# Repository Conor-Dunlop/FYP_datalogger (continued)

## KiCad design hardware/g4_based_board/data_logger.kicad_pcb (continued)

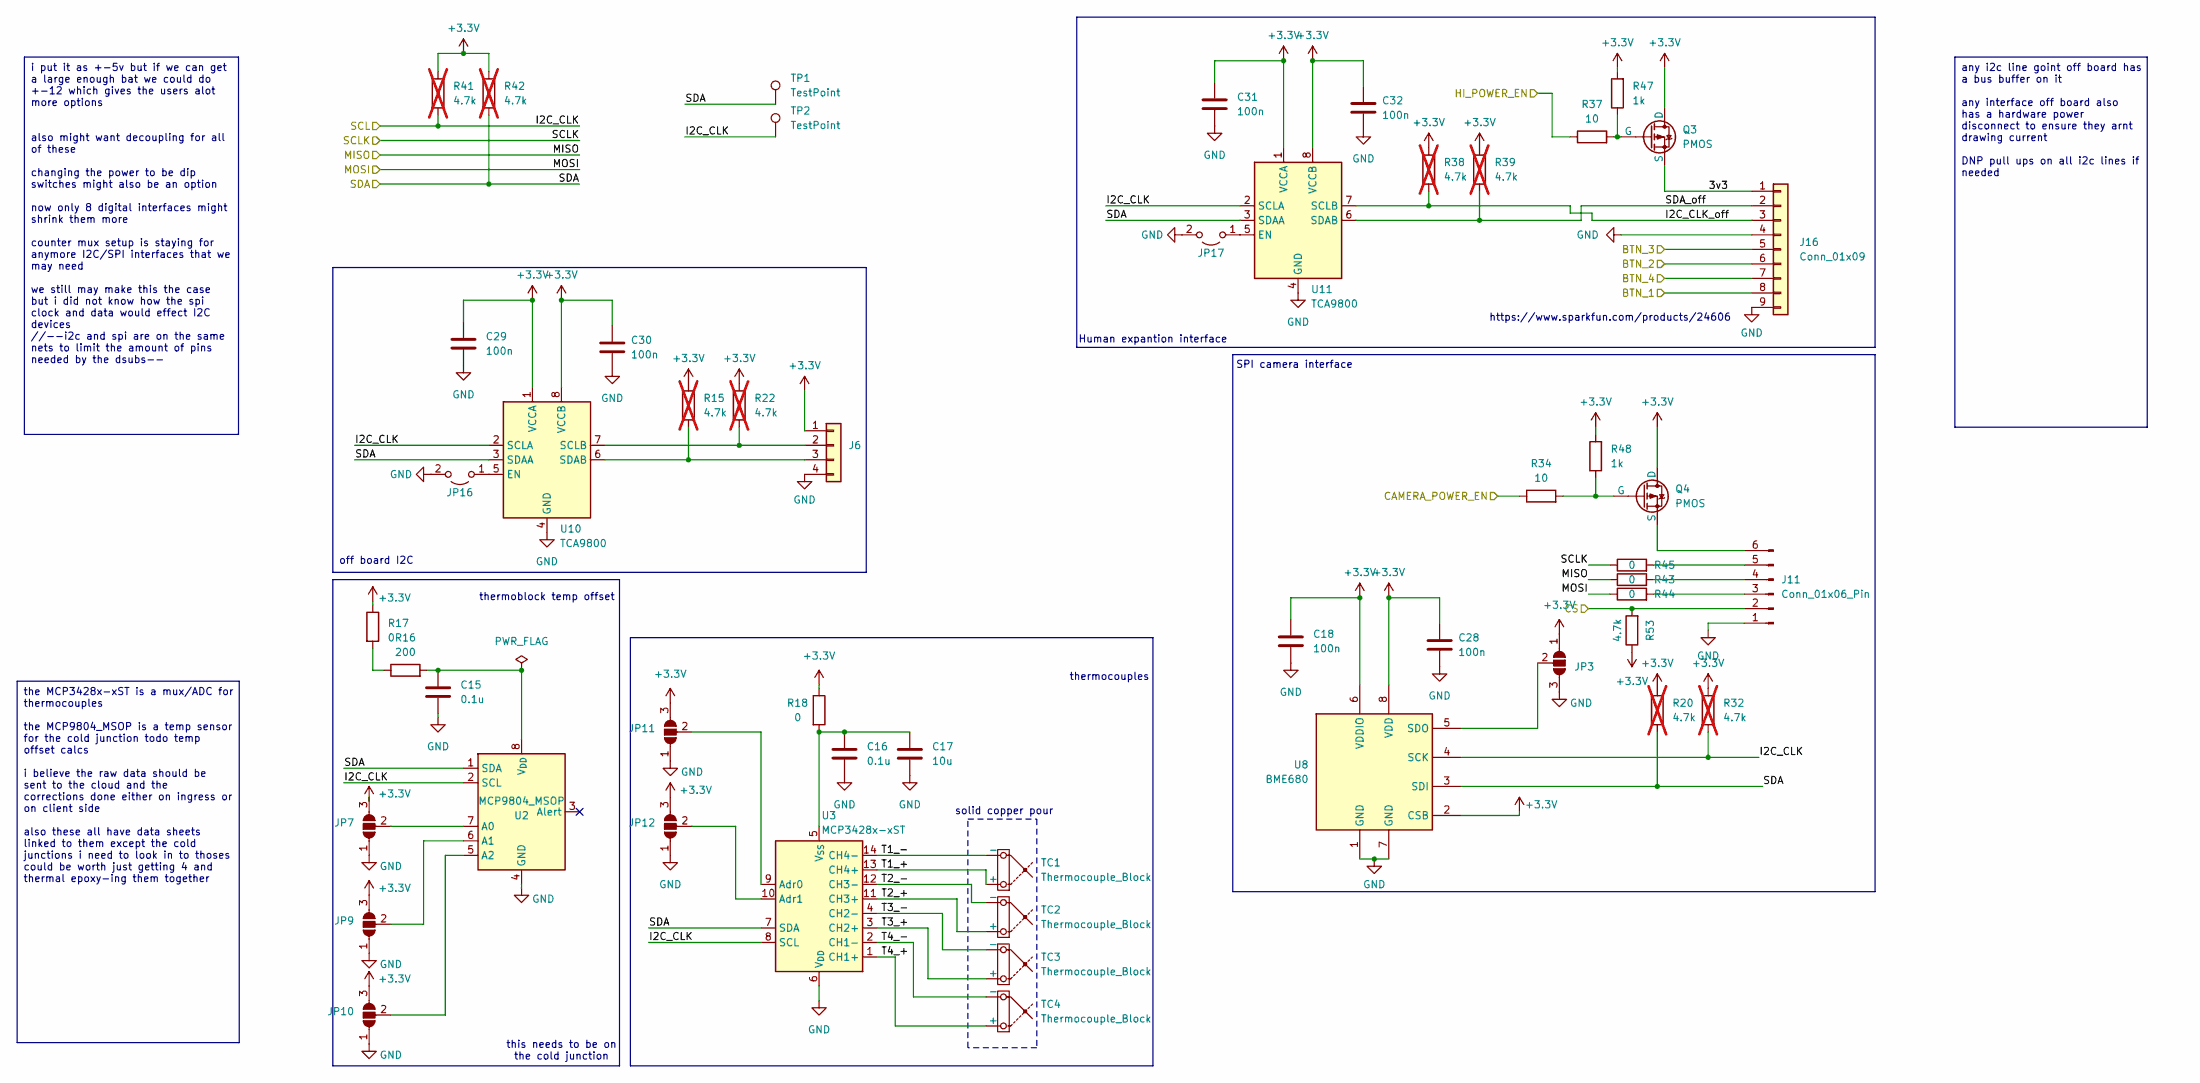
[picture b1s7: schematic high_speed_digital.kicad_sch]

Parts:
C15, C16: 0.1u; C_0603_1608Metric_Pad1.08x0.95mm_HandSolder
C17: 10u; C_0603_1608Metric_Pad1.08x0.95mm_HandSolder
C18, C28, C29, C30, C31, C32: 100n; C_0603_1608Metric_Pad1.08x0.95mm_HandSolder
J6: Conn_01x04; PinHeader_1x04_P2.54mm_Vertical
J11: Conn_01x06_Pin; JST_XH_B6B-XH-A_1x06_P2.50mm_Vertical
J16: Conn_01x09; JST_XH_B9B-XH-A_1x09_P2.50mm_Vertical
JP3, JP7, JP9, JP10, JP11, JP12: SolderJumper-3_P1.3mm_Open_RoundedPad1.0x1.5mm
JP16, JP17: Jumper_2_Open; SolderJumper-2_P1.3mm_Open_TrianglePad1.0x1.5mm
Q3, Q4: PMOS; SOT-23-3
R15, R20, R22, R32, R38, R39, R41, R42: 4.7k; R_0603_1608Metric_Pad0.98x0.95mm_HandSolder; not fitted
R16: 200; R_0603_1608Metric_Pad0.98x0.95mm_HandSolder
R17, R18, R43, R44, R45: 0; R_0603_1608Metric_Pad0.98x0.95mm_HandSolder
R34, R37: 10; R_0603_1608Metric_Pad0.98x0.95mm_HandSolder
R47, R48: 1k; R_0603_1608Metric_Pad0.98x0.95mm_HandSolder
R53: 4.7k; R_0603_1608Metric_Pad0.98x0.95mm_HandSolder
TC1, TC2, TC3, TC4: Thermocouple_Block; TerminalBlock_Altech_AK300-2_P5.00mm
TP1, TP2: TestPoint; TestPoint_Keystone_5015_Micro-Minature
U2: MCP9804_MSOP; MSOP-8_3x3mm_P0.65mm
U3: MCP3428x-xST; TSSOP-14_4.4x5mm_P0.65mm
U8: BME680; Bosch_LGA-8_3x3mm_P0.8mm_ClockwisePinNumbering
U10, U11: TCA9800; VSSOP-8_3.0x3.0mm_P0.65mm

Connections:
+3.3V: C18.1, C28.1, C29.1, C30.1, C31.1, C32.1, J6.1, JP3.1 (A), JP7.3 (B), JP9.3 (B), JP10.3 (B), JP11.3 (B), JP12.3 (B), Q3.1 (D), Q4.1 (D), R15.1, R17.1, R18.1, R20.1, R22.1, R32.1, R38.1, R39.1, R41.1, R42.1, R47.2, R48.2, R53.1, U8.2 (CSB), U8.6 (VDDIO), U8.8 (VDD), U10.1 (VCCA), U10.8 (VCCB), U11.1 (VCCA), U11.8 (VCCB); also elsewhere on the board
/high_speed_digital/BTN_1: J16.8; also elsewhere on the board
/high_speed_digital/BTN_2: J16.6; also elsewhere on the board
/high_speed_digital/BTN_3: J16.5; also elsewhere on the board
/high_speed_digital/BTN_4: J16.7; also elsewhere on the board
/high_speed_digital/CAMERA_POWER_EN: R34.1; also elsewhere on the board
/high_speed_digital/CS: J11.2, R53.2; also elsewhere on the board
/high_speed_digital/HI_POWER_EN: R37.1; also elsewhere on the board
/high_speed_digital/MISO: R43.1; also elsewhere on the board
/high_speed_digital/MOSI: R44.1; also elsewhere on the board
/high_speed_digital/SCLK: R45.1; also elsewhere on the board
/high_speed_digital/T1_+: TC1.1 (+), U3.13 (CH4+)
/high_speed_digital/T1_-: TC1.2 (-), U3.14 (CH4-)
/high_speed_digital/T2_+: TC2.1 (+), U3.11 (CH3+)
/high_speed_digital/T2_-: TC2.2 (-), U3.12 (CH3-)
/high_speed_digital/T3_+: TC3.1 (+), U3.3 (CH2+)
/high_speed_digital/T3_-: TC3.2 (-), U3.4 (CH2-)
/high_speed_digital/T4_+: TC4.1 (+), U3.1 (CH1+)
/high_speed_digital/T4_-: TC4.2 (-), U3.2 (CH1-)
GND: C15.2, C16.2, C17.2, C18.2, C28.2, C29.2, C30.2, C31.2, C32.2, J6.4, J11.1, J16.4, J16.9, JP3.3 (B), JP7.1 (A), JP9.1 (A), JP10.1 (A), JP11.1 (A), JP12.1 (A), JP16.2 (B), JP17.2 (B), U2.4 (GND), U3.6 (V_{DD}), U8.1 (GND), U8.7 (GND), U10.4 (GND), U11.4 (GND); also elsewhere on the board
unnamed: J6.2, R22.2, U10.7 (SCLB)
unnamed: J6.3, R15.2, U10.6 (SDAB)
unnamed: J11.3, R44.2
unnamed: J11.4, R43.2
unnamed: J11.5, R45.2
unnamed: J11.6, Q4.3 (S)
unnamed: J16.1, Q3.3 (S)
unnamed: J16.2, R39.2, U11.6 (SDAB)
unnamed: J16.3, R38.2, U11.7 (SCLB)
unnamed: JP3.2 (C), U8.5 (SDO)
unnamed: JP7.2 (C), U2.7 (A0)
unnamed: JP9.2 (C), U2.6 (A1)
unnamed: JP10.2 (C), U2.5 (A2)
unnamed: JP11.2 (C), U3.9 (Adr0)
unnamed: JP12.2 (C), U3.10 (Adr1)
unnamed: JP16.1 (A), U10.5 (EN)
unnamed: JP17.1 (A), U11.5 (EN)
unnamed: Q3.2 (G), R37.2, R47.1
unnamed: Q4.2 (G), R34.2, R48.1
unnamed: R16.1, R17.2
unnamed: C15.1, R16.2, U2.8 (V_{DD})
unnamed: C16.1, C17.1, R18.2, U3.5 (V_{SS})

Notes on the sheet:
i put it as +-5v but if we can get a large enough bat we could do +-12 which gives the users alot more options also might want decoupling for all of these changing the power to be dip switches might also be an option now only 8 digital interfaces might shrink them more counter mux setup is staying 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
any i2c line goint off board has a bus buffer on it any interface off board also has a hardware power disconnect to ensure they arnt drawing current DNP pull ups on all i2c lines if needed
the MCP3428x-xST is a mux/ADC for thermocouples the MCP9804_MSOP is a temp sensor for the cold junction todo temp offset calcs i believe the raw data should be sent to the cloud and the corrections done either on ingress or on client side also these all have data sheets linked to them except the co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
off board I2C
solid copper pour
https://www.sparkfun.com/products/24606
Human expantion interface
thermocouples
this needs to be on the cold junction
SPI camera interface
thermoblock temp offset

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
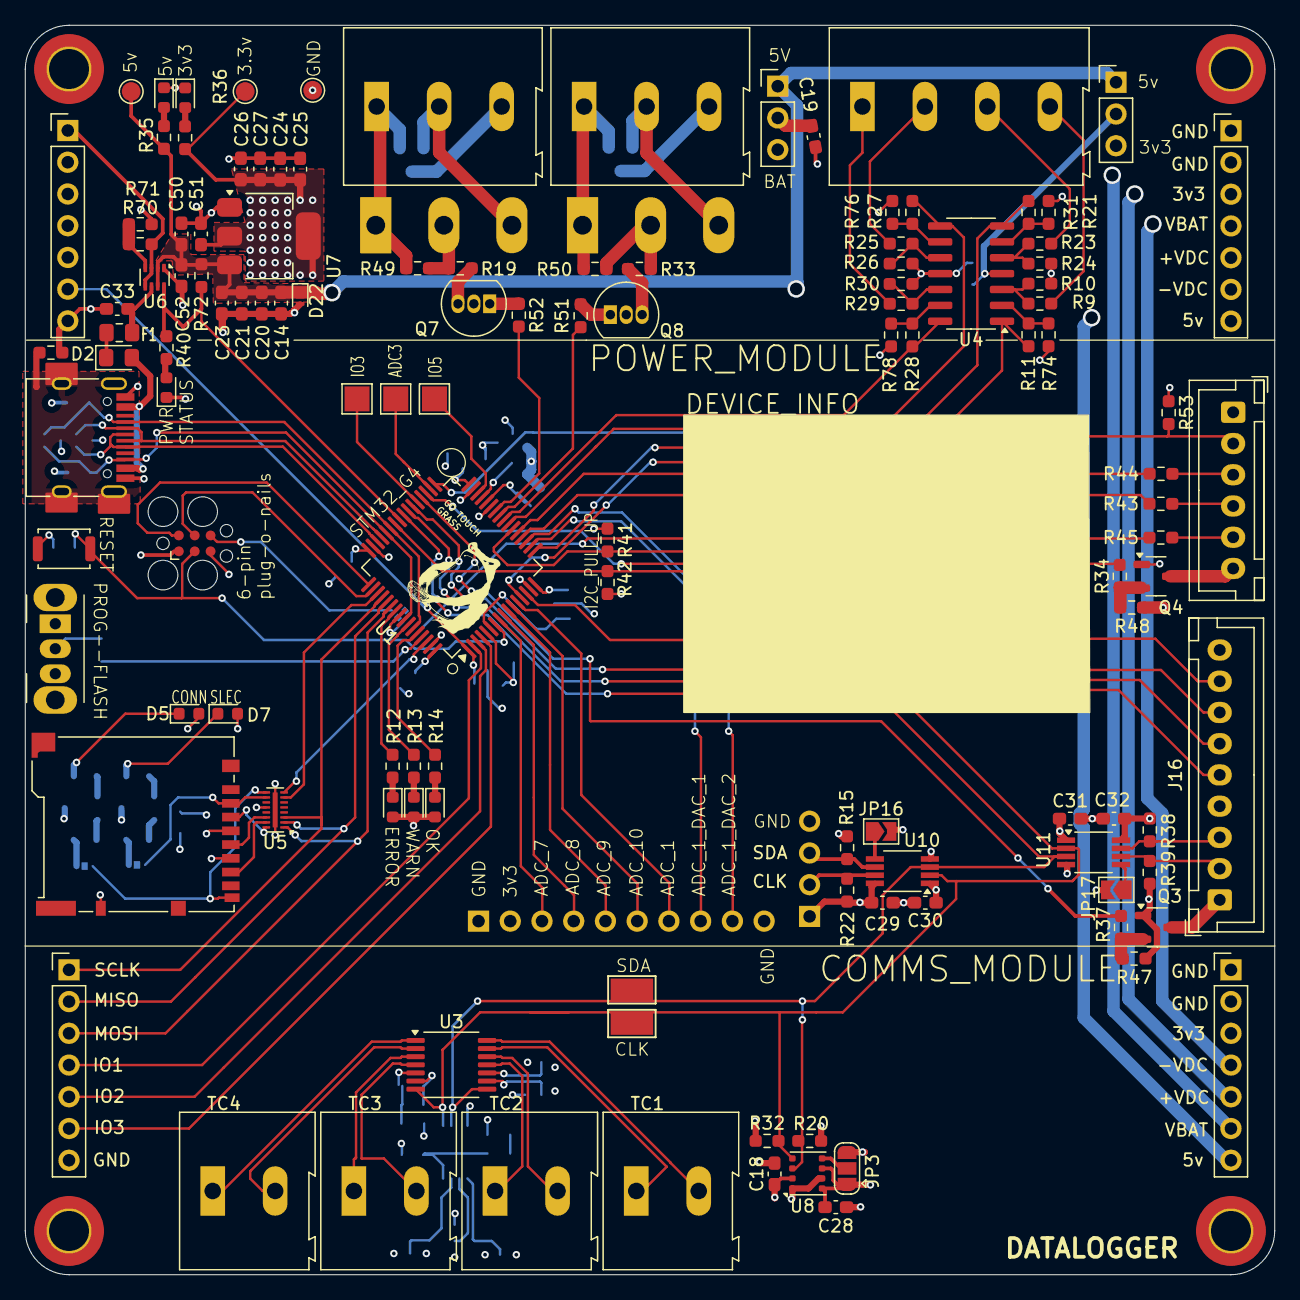
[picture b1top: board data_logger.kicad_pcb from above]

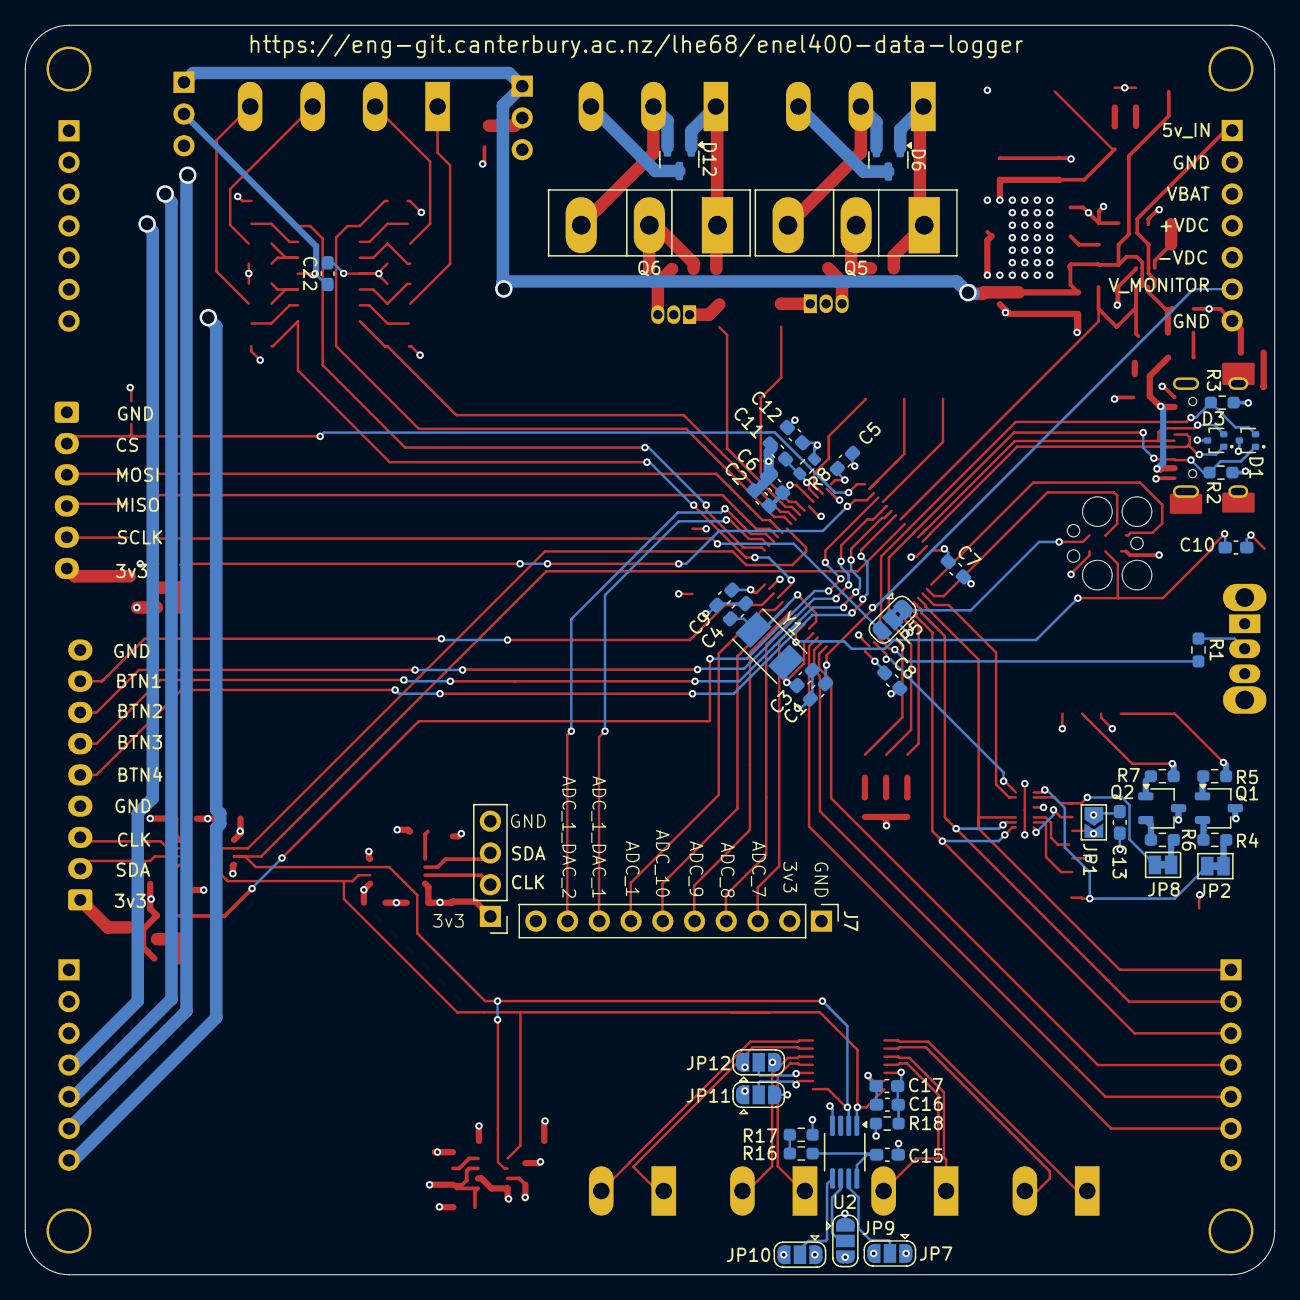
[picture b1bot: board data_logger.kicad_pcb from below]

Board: 4 copper layers, 100.0 x 100.0 mm, 175 parts (49 on the bottom side), 137 nets.

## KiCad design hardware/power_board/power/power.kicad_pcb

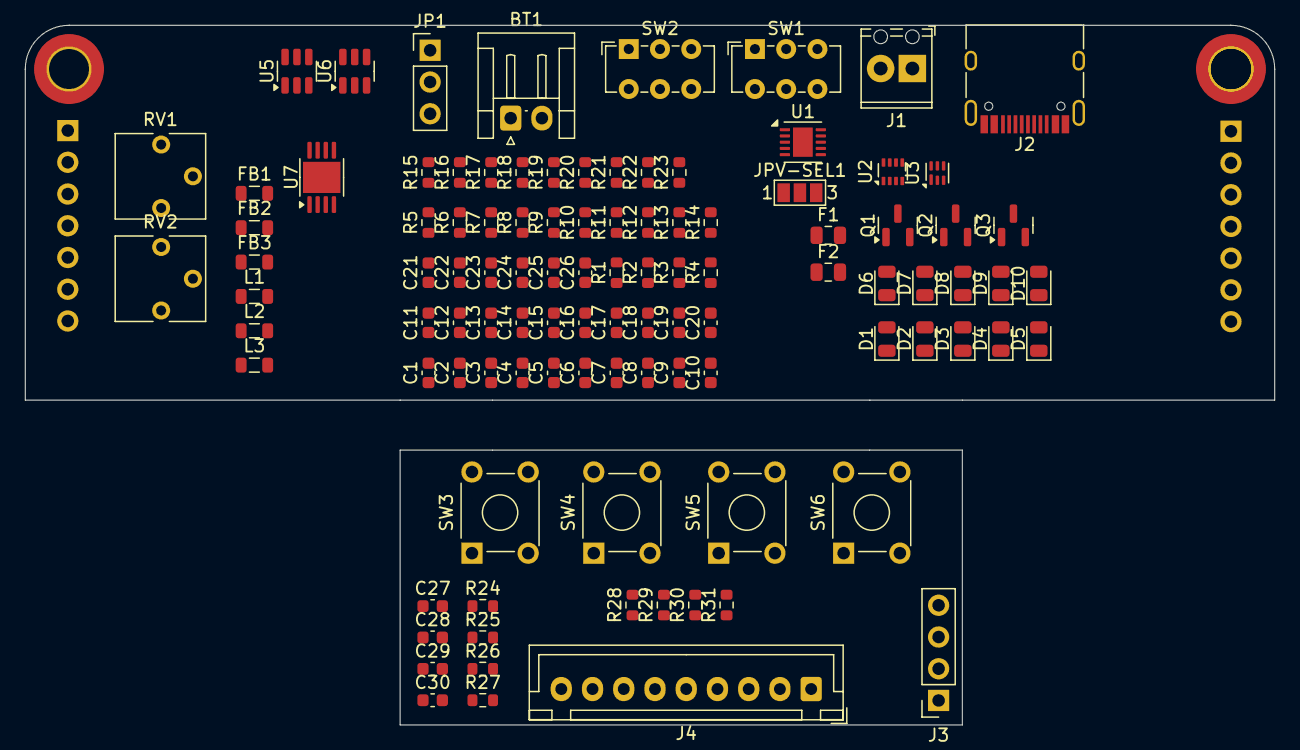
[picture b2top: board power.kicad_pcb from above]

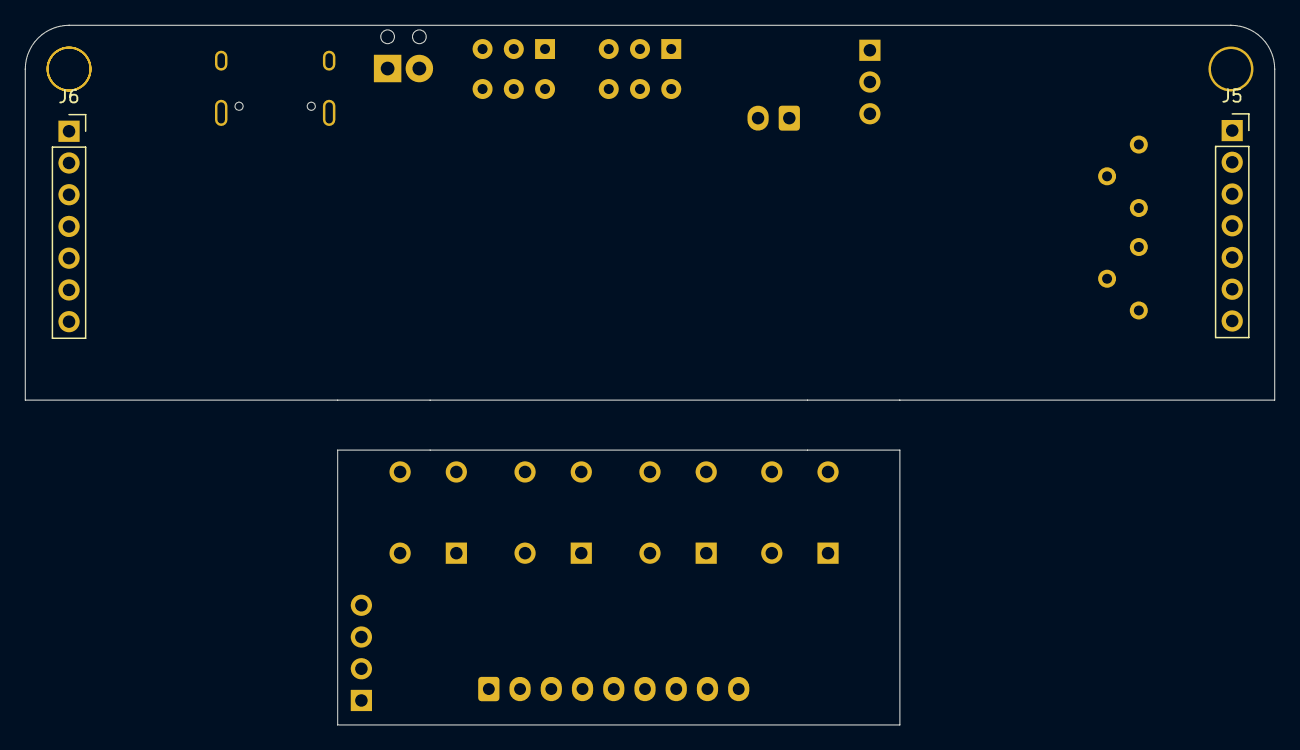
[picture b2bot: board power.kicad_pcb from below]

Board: 2 copper layers, 100.0 x 30.0 mm, 106 parts (2 on the bottom side), 70 nets, no tracks yet.

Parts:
BT1: Battery_Cell; JST_EH_S2B-EH_1x02_P2.50mm_Horizontal
C1, C2, C3, C4, C5, C6, C7, C8, C9, C10, C11, C13, C17, C18, C19, C23, C24: 10u; C_0603_1608Metric
C12, C14: 0.1u; C_0603_1608Metric
C15, C16, C27, C28, C29, C30: C; C_0603_1608Metric
C20, C25, C26: 22u; C_0603_1608Metric
C21, C22: 100n; C_0603_1608Metric
D1: D_Zener; D_0805_2012Metric
D2, D3, D5: D_Schottky; D_0805_2012Metric
D4, D9: CD4148W; D_0805_2012Metric
D6, D7, D8, D10: LED; D_0805_2012Metric
F1: Fuse; Fuse_0805_2012Metric
F2: 2A; Fuse_0805_2012Metric
FB1, FB2, FB3: FerriteBead; L_0805_2012Metric
H2: MountingHole_Pad; MountingHole_3.2mm_M3_DIN965_Pad_TopOnly
J1: Screw_Terminal_01x02; TerminalBlock_Phoenix_MPT-0,5-2-2.54_1x02_P2.54mm_Horizontal
J2: USB_C_Receptacle_USB2.0_16P; USB_C_Receptacle_HRO_TYPE-C-31-M-12
J3: Conn_01x04_Pin; PinSocket_1x04_P2.54mm_Vertical
J4: Conn_01x09; JST_XH_B9B-XH-A_1x09_P2.50mm_Vertical
J5, J6: Conn_01x07_Socket; PinSocket_1x07_P2.54mm_Vertical
JP1: Jumper_3_Bridged12; PinHeader_1x03_P2.54mm_Vertical
JPV-SEL1: Jumper_3_Open; SolderJumper-3_P1.3mm_Open_Pad1.0x1.5mm_NumberLabels
L1: 2.2UH3A; L_0805_2012Metric
L2, L3: 3.3uH; L_0805_2012Metric
Q1: PMOS; SOT-23
Q2, Q3: NMOS; SOT-23
R1, R2, R24, R25, R26, R27, R28, R29, R30, R31: R; R_0603_1608Metric
R3, R4: 5.1k; R_0603_1608Metric
R5, R6, R7: 470; R_0603_1608Metric
R8: 2k2; R_0603_1608Metric
R9: 1k; R_0603_1608Metric
R10: 16.9k; R_0603_1608Metric
R11: 5k; R_0603_1608Metric
R12, R13, R20, R22: 10k; R_0603_1608Metric
R14: 330; R_0603_1608Metric
R15, R17: 750k; R_0603_1608Metric
R16, R18: 100k; R_0603_1608Metric
R19, R21: 52.3k; R_0603_1608Metric
R23: 4.7k; R_0603_1608Metric
RV1, RV2: 100k; Potentiometer_Vishay_T73YP_Vertical
SW1, SW2: SW_SPST; SW_E-Switch_EG1271_SPDT
SW3, SW4, SW5, SW6: SW_Push; SW_TH_Tactile_Omron_B3F-10xx
U1: MCP73833-xxx-MF; DFN-10-1EP_3x3mm_P0.5mm_EP1.58x2.35mm
U2: TPS2117; SOT-583-8
U3: BQ297xy; WSON-6_1.5x1.5mm_P0.5mm
U5, U6: AP62150WU; TSOT-23-6
U7: PAM2401; MSOP-8-1EP_3x3mm_P0.65mm_EP2.5x3mm_Mask1.73x2.36mm

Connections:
+3.3V: C7.1, C9.1, C10.1, C11.1, C20.1
+3V3: J3.1, J4.1, R24.1, R25.1, R26.1, R27.1
+5BAT: C23.1, C24.1, D10.2 (A), R17.2, U2.6 (VIN2), U7.7 (OUT)
+5BUS: C26.1, L3.2, R21.1
+5DC: C25.1, D2.2 (A), JP1.1 (A), L2.2, R19.1
+5V: C1.1, C2.1, C3.1, C4.1, C19.1, J5.1, SW2.1 (A)
+BATT: C12.1, C13.1, C14.1, C16.1, F2.1, J5.3, L1.1, R15.2, RV2.3, U1.9 (V_{BAT}), U1.10 (V_{BAT}), U7.3 (VIN)
/D+: J2.A6 (D+), J2.B6 (D+)
/D-: J2.A7 (D-), J2.B7 (D-)
/PG1: D6.1 (K), D7.1 (K), R6.1, R7.1
/POWER_STATUS: R13.2, U2.8 (ST)
/STAT1: D8.1 (K), R5.1
/V_MCU: J5.6, JPV-SEL1.2 (C)
/īnput_breakoff/BTN1: J4.8, R31.2
/īnput_breakoff/BTN2: J4.6, R29.2
/īnput_breakoff/BTN3: J4.5, R28.2
/īnput_breakoff/BTN4: J4.7, R30.2
/īnput_breakoff/I2C_CLK: J3.3, J4.3
/īnput_breakoff/SDA: J3.2, J4.2
GND: C1.2, C2.2, C3.2, C4.2, C5.2, C6.2, C7.2, C8.2, C9.2, C10.2, C11.2, C12.2, C13.2, C15.2, C16.2, C17.2, C18.2, C19.2, C20.2, C23.2, C24.2, C25.2, C26.2, C27.2, C28.2, C29.2, C30.2, D4.2 (A), D9.2 (A), J1.1, J2.A1 (GND), J2.A12 (GND), J2.B1 (GND), J2.B12 (GND), J3.4, J4.4, J4.9, J5.2, J5.7, Q2.3 (S), R1.2, R2.1, R3.2, R4.1, R8.1, R9.1, R11.2, R16.1, R18.1, R20.2, R22.2, R23.1, RV1.1, RV2.1, U1.5 (V_{SS}), U2.1 (GND), U5.1 (GND), U6.1 (GND), U7.4 (AGND), U7.8 (PGND)
GNDS: H2.1, J2.S1 (SHIELD), R1.1
unnamed: BT1.1 (+), SW1.1 (A)
unnamed: BT1.2 (-), Q3.3 (S), R14.1, U3.4 (VSS)
unnamed: C6.1, F1.2, FB2.1
unnamed: C27.1, R28.1, SW3.2
unnamed: C28.1, R29.1, SW4.2
unnamed: C29.1, R30.1, SW5.2
unnamed: C30.1, R31.1, SW6.2
unnamed: D1.2 (A), Q1.2 (G), R2.2
unnamed: D1.1 (K), D4.1 (K), F1.1, Q1.3 (S)
unnamed: C5.1, D2.1 (K), D3.1 (K), D6.2 (A), D7.2 (A), D8.2 (A), U1.1 (V_{DD}), U1.2 (V_{DD})
unnamed: D5.2 (A), J2.A4 (VBUS), J2.A9 (VBUS), J2.B4 (VBUS), J2.B9 (VBUS)
unnamed: D5.1 (K), FB1.1
unnamed: D10.1 (K), R23.2
unnamed: FB3.1, R13.1, U2.2 (VOUT), U2.7 (VOUT)
unnamed: J1.2, Q1.1 (D)
unnamed: J2.A5 (CC1), R4.2
unnamed: J2.B5 (CC2), R3.1
unnamed: JP1.2 (C), R10.1, R12.1, U2.3 (VIN1)
unnamed: JPV-SEL1.1 (A), RV1.2
unnamed: JPV-SEL1.3 (B), RV2.2
unnamed: Q2.1 (D), Q3.1 (D)
unnamed: Q2.2 (G), U3.2 (Cout)
unnamed: Q3.2 (G), U3.3 (Dout)
unnamed: R24.2, SW6.1
unnamed: R25.2, SW3.1
unnamed: R26.2, SW4.1
unnamed: R27.2, SW5.1
unnamed: F2.2, SW1.2 (B)
unnamed: C15.1, FB3.2, SW2.2 (B)
unnamed: R9.2, U1.6 (PROG)
unnamed: R5.2, U1.3 (STAT1)
unnamed: R6.2, U1.4 (STAT2)
unnamed: R7.2, U1.7 (~PG)
unnamed: R12.2, U2.5 (MODE)
unnamed: R10.2, R11.1, U2.4 (PR1)
unnamed: C14.2, R14.2, U3.5 (BAT)
unnamed: R8.2, U3.6 (V-)
unnamed: C21.2, U5.6 (BST)
unnamed: R19.2, R20.1, U5.4 (FB)
unnamed: C21.1, L2.1, U5.2 (SW)
unnamed: C22.2, U6.6 (BST)
unnamed: R21.2, R22.1, U6.4 (FB)
unnamed: C22.1, L3.1, U6.2 (SW)
unnamed: R15.1, U7.2 (EN)
unnamed: R17.1, R18.2, U7.5 (FB)
unnamed: L1.2, U7.1 (LX)
unnamed: R16.2, U7.6 (RSET)
VBUS: C8.1, C18.1, D3.2 (A), D9.1 (K), FB1.2, JP1.3 (B), U6.3 (VIN), U6.5 (EN)
VDC: C17.1, FB2.2, RV1.3, U5.3 (VIN), U5.5 (EN)

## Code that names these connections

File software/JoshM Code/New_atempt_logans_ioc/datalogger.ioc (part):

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Mcu.Name=STM32G431R(6-8-B)Tx
Mcu.Package=LQFP64
Mcu.UserName=STM32G431RBTx
PA0.GPIOParameters=GPIO_Label
PA0.GPIO_Label=ADC_1
PA0.Mode=IN1-Single-Ended
PA0.Signal=ADC1_IN1
PA1.GPIOParameters=GPIO_Label
PA1.GPIO_Label=ADC_2
PA1.Mode=IN2-Single-Ended
PA1.Signal=ADC1_IN2
PA10.Mode=EnableDeadBattery
PA10.Signal=UCPD1_DBCC2
PA11.Mode=Device
PA11.Signal=USB_DM
PA12.Mode=Device
PA12.Signal=USB_DP
PA13.Mode=Serial_Wire
PA13.Signal=SYS_JTMS-SWDIO
PA14.Mode=Serial_Wire
PA14.Signal=SYS_JTCK-SWCLK
PA15.GPIOParameters=GPIO_PuPd,GPIO_Label,GPIO_ModeDefaultOutputPP
PA15.GPIO_Label=ERROR_STATUS
PA15.GPIO_ModeDefaultOutputPP=GPIO_MODE_OUTPUT_PP
PA15.GPIO_PuPd=GPIO_PULLDOWN
PA15.Signal=GPIO_Output
PA2.GPIOParameters=GPIO_Label
PA2.GPIO_Label=WAKE_BTN
PA2.Signal=GPIO_Input
PA3.GPIOParameters=GPIO_Label
PA3.GPIO_Label=ADC_4
PA3.Mode=IN4-Single-Ended
PA3.Signal=ADC1_IN4
PA4.GPIOParameters=GPIO_Label
PA4.GPIO_Label=ADC_DAC_1
PA4.Signal=COMP_DAC11_group
PA5.GPIOParameters=GPIO_Label
PA5.GPIO_Label=ADC_DAC_2
PA5.Signal=COMP_DAC12_group
PA6.Mode=Full_Duplex_Master
PA6.Signal=SPI1_MISO
PA7.Mode=Full_Duplex_Master
PA7.Signal=SPI1_MOSI
PA8.Mode=I2C
PA8.Signal=I2C2_SDA
PA9.Mode=EnableDeadBattery
PA9.Signal=UCPD1_DBCC1
PB0.GPIOParameters=GPIO_Label
PB0.GPIO_Label=PWM_OUT
PB0.Mode=IN15-Single-Ended
PB0.Signal=ADC1_IN15
PB1.GPIOParameters=GPIO_Label
PB1.GPIO_Label=DIGITAL_IO_6
PB1.Signal=GPIO_Output
PB10.GPIOParameters=GPIO_Label
PB10.GPIO_Label=DIGITAL_IO_5
PB10.Signal=GPIO_Output
PB11.GPIOParameters=GPIO_Label
PB11.GPIO_Label=DIGITAL_IO_4
PB11.Signal=GPIO_Input
PB12.GPIOParameters=GPIO_Label
PB12.GPIO_Label=ADC_3
PB12.Mode=IN11-Single-Ended
PB12.Signal=ADC1_IN11
PB13.GPIOParameters=GPIO_Label
PB13.GPIO_Label=DIGITAL_IO_3
PB13.Signal=GPIO_Output
PB14.Mode=IN5-Single-Ended
PB14.Signal=ADC1_IN5
PB15.GPIOParameters=GPIO_Label
PB15.GPIO_Label=DIGITAL_IO_1
PB15.Signal=GPIO_Output
PB2.GPIOParameters=GPIO_Label
PB2.GPIO_Label=PWR_STATUS
PB2.Signal=GPIO_Input
PB3.Signal=SharedStack_PB3
PB3.Stacked=true
PB4.Mode=Sink_AllSignals
PB4.Signal=UCPD1_CC2
PB5.GPIOParameters=GPIO_PuPd,GPIO_Label
PB5.GPIO_Label=WARN_STATUS
PB5.GPIO_PuPd=GPIO_PULLDOWN
PB5.Signal=GPIO_Output
PB6.Mode=Sink_AllSignals
PB6.Signal=UCPD1_CC1
PB7.GPIOParameters=GPIO_PuPd,GPIO_Label
PB7.GPIO_Label=STATUS
PB7.GPIO_PuPd=GPIO_PULLDOWN
PB7.Signal=GPIO_Output
PB9.GPIOParameters=GPIO_Label
PB9.GPIO_Label=SD_CARD_DETECT
PB9.Signal=GPIO_Input
PC0.GPIOParameters=GPIO_Label
PC0.GPIO_Label=SIG_4
PC0.Mode=IN6-Single-Ended
PC0.Signal=ADC1_IN6
PC1.GPIOParameters=GPIO_Label
PC1.GPIO_Label=SIG_2
PC1.Mode=IN7-Single-Ended
PC1.Signal=ADC1_IN7
PC10.Mode=Full_Duplex_Master
PC10.Signal=SPI3_SCK
PC11.Mode=Full_Duplex_Master
PC11.Signal=SPI3_MISO
PC12.Mode=Full_Duplex_Master
PC12.Signal=SPI3_MOSI
PC13.GPIOParameters=GPIO_Label
PC13.GPIO_Label=DOWN_BTN
PC13.Signal=GPIO_Input
PC14-OSC32_IN.GPIOParameters=GPIO_Label
PC14-OSC32_IN.GPIO_Label=UP_BTN
PC14-OSC32_IN.Signal=GPIO_Input
PC15-OSC32_OUT.GPIOParameters=GPIO_Label
PC15-OSC32_OUT.GPIO_Label=ENTER_BTN
PC15-OSC32_OUT.Signal=GPIO_Input
PC2.GPIOParameters=GPIO_Label
PC2.GPIO_Label=ADC_9
PC2.Mode=IN8-Single-Ended
PC2.Signal=ADC1_IN8
PC3.GPIOParameters=GPIO_Label
PC3.GPIO_Label=ADC_10
PC3.Mode=IN9-Single-Ended
PC3.Signal=ADC1_IN9
PC4.Mode=I2C
PC4.Signal=I2C2_SCL
PC5.GPIOParameters=GPIO_Label
PC5.GPIO_Label=ADC-12
PC5.Mode=IN11-Single-Ended
PC5.Signal=ADC2_IN11
PC6.GPIOParameters=GPIO_Label
PC6.GPIO_Label=COMMS_EN_1
PC6.Signal=GPIO_Output
PC7.GPIOParameters=GPIO_Label
PC7.GPIO_Label=COMMS_EN_2
PC7.Signal=GPIO_Output
PC8.GPIOParameters=GPIO_Label
PC8.GPIO_Label=COMMS_EN_3
PC8.Signal=GPIO_Output
PC9.GPIOParameters=GPIO_Label
PC9.GPIO_Label=SD_SELECT
PC9.Signal=GPIO_Output
PF0-OSC_IN.Mode=HSE-External-Oscillator
PF0-OSC_IN.Signal=RCC_OSC_IN
PF1-OSC_OUT.Mode=HSE-External-Oscillator
PF1-OSC_OUT.Signal=RCC_OSC_OUT
RCC.HSE_VALUE=8000000
RCC.SYSCLKFreq_VALUE=16000000
board=custom

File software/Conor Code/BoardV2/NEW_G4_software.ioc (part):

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Mcu.Name=STM32G431R(6-8-B)Tx
Mcu.Package=LQFP64
Mcu.UserName=STM32G431RBTx
PA0.GPIOParameters=GPIO_Label
PA0.GPIO_Label=ADC_1
PA0.Mode=IN1-Single-Ended
PA0.Signal=ADC1_IN1
PA1.GPIOParameters=GPIO_Label
PA1.GPIO_Label=OPAMP_SIG_2
PA1.Mode=IN2-Single-Ended
PA1.Signal=ADC1_IN2
PA10.Mode=EnableDeadBattery
PA10.Signal=UCPD1_DBCC2
PA11.Mode=Device
PA11.Signal=USB_DM
PA12.Mode=Device
PA12.Signal=USB_DP
PA13.Mode=Serial_Wire
PA13.Signal=SYS_JTMS-SWDIO
PA14.Mode=Serial_Wire
PA14.Signal=SYS_JTCK-SWCLK
PA15.GPIOParameters=GPIO_PuPd,GPIO_Label,GPIO_ModeDefaultOutputPP
PA15.GPIO_Label=SD_CARD_EN
PA15.GPIO_ModeDefaultOutputPP=GPIO_MODE_OUTPUT_PP
PA15.GPIO_PuPd=GPIO_NOPULL
PA15.Signal=GPIO_Output
PA2.GPIOParameters=GPIO_Label
PA2.GPIO_Label=WAKE_BTN
PA2.Signal=GPIO_Input
PA3.GPIOParameters=GPIO_Label
PA3.GPIO_Label=OPAMP_SIG_4
PA3.Mode=IN4-Single-Ended
PA3.Signal=ADC1_IN4
PA4.GPIOParameters=GPIO_Label
PA4.GPIO_Label=ADC_DAC_1
PA4.Signal=COMP_DAC11_group
PA5.GPIOParameters=GPIO_Label
PA5.GPIO_Label=ADC_DAC_2
PA5.Signal=COMP_DAC12_group
PA6.Mode=Full_Duplex_Master
PA6.Signal=SPI1_MISO
PA7.Mode=Full_Duplex_Master
PA7.Signal=SPI1_MOSI
PA8.Mode=I2C
PA8.Signal=I2C2_SDA
PA9.Mode=EnableDeadBattery
PA9.Signal=UCPD1_DBCC1
PB0.GPIOParameters=GPIO_Label
PB0.GPIO_Label=OPAMP_SIG_1
PB0.Mode=IN15-Single-Ended
PB0.Signal=ADC1_IN15
PB1.GPIOParameters=GPIO_Label
PB1.GPIO_Label=PWM_2
PB1.Signal=GPIO_Output
PB10.GPIOParameters=GPIO_Label
PB10.GPIO_Label=DIGITAL_IO_5
PB10.Signal=GPIO_Output
PB11.GPIOParameters=GPIO_Label
PB11.GPIO_Label=DIGITAL_IO_6
PB11.Signal=GPIO_Input
PB12.GPIOParameters=GPIO_Label
PB12.GPIO_Label=ADC_3
PB12.Mode=IN11-Single-Ended
PB12.Signal=ADC1_IN11
PB13.GPIOParameters=GPIO_Label
PB13.GPIO_Label=DIGITAL_IO_1
PB13.Signal=GPIO_Output
PB14.GPIOParameters=GPIO_Label
PB14.GPIO_Label=DIGITAL_IO_2
PB14.Mode=IN5-Single-Ended
PB14.Signal=ADC1_IN5
PB15.GPIOParameters=GPIO_Label
PB15.GPIO_Label=DIGITAL_IO_3
PB15.Signal=GPIO_Output
PB2.GPIOParameters=GPIO_Label
PB2.GPIO_Label=PWM_1
PB2.Signal=GPIO_Input
PB3.Signal=SharedStack_PB3
PB3.Stacked=true
PB4.Mode=Sink_AllSignals
PB4.Signal=UCPD1_CC2
PB5.GPIOParameters=GPIO_PuPd,GPIO_Label
PB5.GPIO_Label=WARN_STATUS
PB5.GPIO_PuPd=GPIO_NOPULL
PB5.Signal=GPIO_Output
PB6.Mode=Sink_AllSignals
PB6.Signal=UCPD1_CC1
PB7.GPIOParameters=PinState,GPIO_PuPd,GPIO_Label,GPIO_ModeDefaultOutputPP
PB7.GPIO_Label=OK_STATUS
PB7.GPIO_ModeDefaultOutputPP=GPIO_MODE_OUTPUT_PP
PB7.GPIO_PuPd=GPIO_NOPULL
PB7.PinState=GPIO_PIN_RESET
PB7.Signal=GPIO_Output
PB9.GPIOParameters=GPIO_Label
PB9.GPIO_Label=SD_CARD_DETECT
PB9.Signal=GPIO_Input
PC0.GPIOParameters=GPIO_Label
PC0.GPIO_Label=ADC_7
PC0.Mode=IN6-Single-Ended
PC0.Signal=ADC1_IN6
PC1.GPIOParameters=GPIO_Label
PC1.GPIO_Label=ADC_8
PC1.Mode=IN7-Single-Ended
PC1.Signal=ADC1_IN7
PC10.Mode=Full_Duplex_Master
PC10.Signal=SPI3_SCK
PC11.Mode=Full_Duplex_Master
PC11.Signal=SPI3_MISO
PC12.Mode=Full_Duplex_Master
PC12.Signal=SPI3_MOSI
PC13.GPIOParameters=GPIO_Label
PC13.GPIO_Label=COMMS_IO_1
PC13.Signal=GPIO_Input
PC14-OSC32_IN.GPIOParameters=GPIO_Label
PC14-OSC32_IN.GPIO_Label=COMMS_IO_2
PC14-OSC32_IN.Signal=GPIO_Input
PC15-OSC32_OUT.GPIOParameters=GPIO_Label
PC15-OSC32_OUT.GPIO_Label=COMMS_IO_3
PC15-OSC32_OUT.Signal=GPIO_Input
PC2.GPIOParameters=GPIO_Label
PC2.GPIO_Label=ADC_9
PC2.Mode=IN8-Single-Ended
PC2.Signal=ADC1_IN8
PC3.GPIOParameters=GPIO_Label
PC3.GPIO_Label=ADC_10
PC3.Mode=IN9-Single-Ended
PC3.Signal=ADC1_IN9
PC4.Mode=I2C
PC4.Signal=I2C2_SCL
PC5.GPIOParameters=GPIO_Label
PC5.GPIO_Label=OPAMP_SIG_3
PC5.Mode=IN11-Single-Ended
PC5.Signal=ADC2_IN11
PC6.GPIOParameters=GPIO_Label
PC6.GPIO_Label=DOWN_BTN
PC6.Signal=GPIO_Output
PC7.GPIOParameters=GPIO_Label
PC7.GPIO_Label=UP_BTN
PC7.Signal=GPIO_Output
PC8.GPIOParameters=GPIO_Label
PC8.GPIO_Label=ENTER_BTN
PC8.Signal=GPIO_Output
PC9.GPIOParameters=GPIO_Label
PC9.GPIO_Label=PWR_STATUS
PC9.Signal=GPIO_Output
PD2.GPIOParameters=GPIO_Label
PD2.GPIO_Label=ERROR_STATUS
PD2.Signal=GPIO_Output
PF0-OSC_IN.Mode=HSE-External-Oscillator
PF0-OSC_IN.Signal=RCC_OSC_IN
PF1-OSC_OUT.Mode=HSE-External-Oscillator
PF1-OSC_OUT.Signal=RCC_OSC_OUT
RCC.HSE_VALUE=8000000
RCC.SYSCLKFreq_VALUE=16000000
board=custom

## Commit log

2024-03-01 basic templates added
2024-03-02 removed default template text
2024-03-02 added added a block diagram and some basic requirements
2024-03-04 reconfigured project structure and added lui's board template
2024-03-06 added custom symbol for multiplexer
2024-03-06 basic multiplexed digital interface for spi and i2c
2024-03-06 added sd card and status leds
2024-03-06 added hierarchical for to reflect changes in project structure and added enable i2c pull ups
2024-03-06 added gitignore to remove local backups from uploading
2024-03-06 added more ignores for kicad auto gen'ed files
2024-03-06 added basic power sheet
2024-03-06 added auto updated files
2024-03-06 added some notes to reqs still work in progress
2024-03-06 updated to fix merge error
2024-03-07 added a 5v linear reg
2024-03-07 added tvs proctection didoes
2024-03-07 removed 8 ports as it was too many
2024-03-07 file for later use
2024-03-07 basic thermocouple sch
2024-03-07 auto updated files
2024-03-09 basic LCD display with i2c port expander
2024-03-09 first desgin of a multi use interface to allow signal and power out on the same lines
2024-03-09 moved the 5v reg to only use the battery as input
2024-03-09 power prioritizer to try and make sure the mcu always has power
2024-03-09 empty sch for an analog amp for the dac ouputs
2024-03-09 slight redesign and added solder jumpers for i2c address select
2024-03-09 changed to thermocouples
2024-03-09 added more hierarchical ports and removed the i2c pull ups
2024-03-09 removed half of the digial interfaces and added the thermocouples and LCD modules in to this sheet
2024-03-09 sheet for the comms hat to go in
2024-03-09 updated list slightly
2024-03-11 added more notes on to the sch
2024-03-11 changed power to be an external module
2024-03-11 added jumpers to the micro SD card as well as a schotty to the VBus of the type c for safety
2024-03-11 removed comms counter and it now uses the one defined in spi_en_expander
2024-03-11 changed to having seprate I2C and SPI lines with switches for power select
2024-03-11 now uses hierarchical sheets
2024-03-11 skew of gpio_connect that also has a power amp on it for use with pins that have a dac
2024-03-11 added docs
2024-03-11 moved out of the high speed digital io and into its own sheet
2024-03-11 new kicad project for psu module for the data logger
2024-03-11 auto updated kicad files
2024-03-14 git thinks something changed in this file
2024-03-14 change mcu to a larger version of the stm32G4 allowing for the spi expander to be removed
2024-03-14 added the tps2117 to swap between usb power and power supply power
2024-03-14 changed 5v on the type c header to VBUS
2024-03-14 updated 5v in for the psu to +5P to distinguish between that and 5v for the pwoer switcher
2024-03-14 added new part the tps2117
2024-03-14 recreated this to refelect the change in mcu
2024-03-14 auto generated files form stm32cubeMX
2024-03-15 added values to resistors
2024-03-15 changed switches to jumpers
2024-03-15 added test point footprint
2024-03-15 fix some erc violations
2024-03-15 removed spi expander and now uses mcu pins for enable
2024-03-15 added power signal for mcu to know what power source its using
2024-03-15 swapped around some cold junctions for ease of routing
2024-03-15 routed lcd and thermocouple modules
2024-03-15 Initial commit of LoRaWAN/WiFi/Bluetooth board
2024-03-18 added an extra tvs diodes to both 3.3v and sd_conn on the sd card
2024-03-18 replaced orignal switch to avoid ERC error
2024-03-18 changed the dac outputs to normal gpio as there was not enough room
2024-03-18 removed protection diodes as the tvs diodes are enough
2024-03-18 changed headers to right layout
2024-03-18 swapped thermocouple layout yet again
2024-03-18 auto updated
2024-03-18 added buttons for interfacing with the mcu
2024-03-18 added usart, buttons and made sure each pin is allocated correctly
2024-03-18 added buttons
2024-03-18 added usart header and attached buttons
2024-03-18 allocated every pin to its use
2024-04-14 generated code for data logger
2024-04-15 rev-1
2024-04-22 updated .ioc to reflect changes make in pcb
2024-04-23 removed lock
2024-04-23 minor addtion and swd header added and usart removed
2024-04-23 updated to reflect change however some user define labs have changed
2024-07-16 added bulk decoupling and status leds
2024-07-16 changed to high side pmos driver
2024-07-16 SD card protection now uses the CM1624, and removed buttons to be off board
2024-07-16 added thermo sensor in here, added BME680, all off board i2c lines now have a bus buffer
2024-07-16 swapped assignment to differnt pins
2024-07-16 upadate to reflect larger changes
2024-07-16 new pcb rev to reflect changes made in sch
2024-07-16 added parts for data logger and powerboard
2024-07-16 basic 1 cell lipo power board
2024-08-03 fixed a minor error in the sch
2024-08-03 basic uart sending code, will also repeat the sent string over USB coms
2024-08-03 basic ESP32 uart repeater, ill make this send it to the webserver later
2024-08-03 chole add the emulator code here
2024-08-05 added helper function for using the ADC
2024-08-05 now sends over a counter, ADC value, a button counter, and a state that is changed with the enter button
2024-08-05 changed button to have pulldown instead of no pull
2024-08-05 now sends data from the data logger to an http server
2024-08-05 .ioc file for new stm board config
2024-08-05 wasnt needed
2024-08-05 basic http server for testing
2024-08-05 uncommented the ssid and password since people would get confused, dont for get to change it to your network
2024-08-07 put emulator on git
2024-08-07 put chloe's stuff on the git
2024-08-14 Add new directory for Conors code
2024-08-14 Add Conors SPI and UART output codes
2024-08-16 get esp32 comms working
2024-08-16 add secrets to gitignore
2024-08-26 Change to most recent local
2024-08-27 Built successfully
2024-08-27 Build works
2024-09-03 fixed error pin not being defined
2024-09-07 add elf testing file
2024-09-11 Add Conors new board code and workspace
2024-09-11 SX1262 STM32 code
2024-09-12 Heltec ESP32 Transmit and Recieve
2024-09-12 Working TX and RX of UART data over lora
2024-09-15 Added 2 tests
2024-09-15 Update V2 with new I2C
2024-09-15 SX1262 SPI testing
2024-09-16 Update conor code
2024-09-16 basic program for new g4 board that has working i2c and usb logging
2024-09-17 Update with logans variables
2024-09-17 Rebuilt
2024-09-17 Switch chip select and move I2C to main
2024-09-17 Add test cases
2024-09-17 New Test Suit
2024-09-17 Add SPI test
2024-09-18 Conor V2 Read I2C write Uart
2024-09-19 updated heltec code
2024-09-19 Added timestamp
2024-09-22 Add new test
2024-09-22 Add new Char transmit
2024-09-27 Add spi and lptim1 ioc and main
2024-09-27 Add new spi and lptim1 ioc and main
2024-09-27 Add temp read sent over spi
2024-10-11 docs for how to program the stm32 datalogger board
2024-10-11 images for programming docs
2024-10-11 basic readme
2024-10-11 added image for readme
2024-10-11 documentation
2024-10-21 FYP final group report
